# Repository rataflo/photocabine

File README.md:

# photocabine
Analogue photo booth

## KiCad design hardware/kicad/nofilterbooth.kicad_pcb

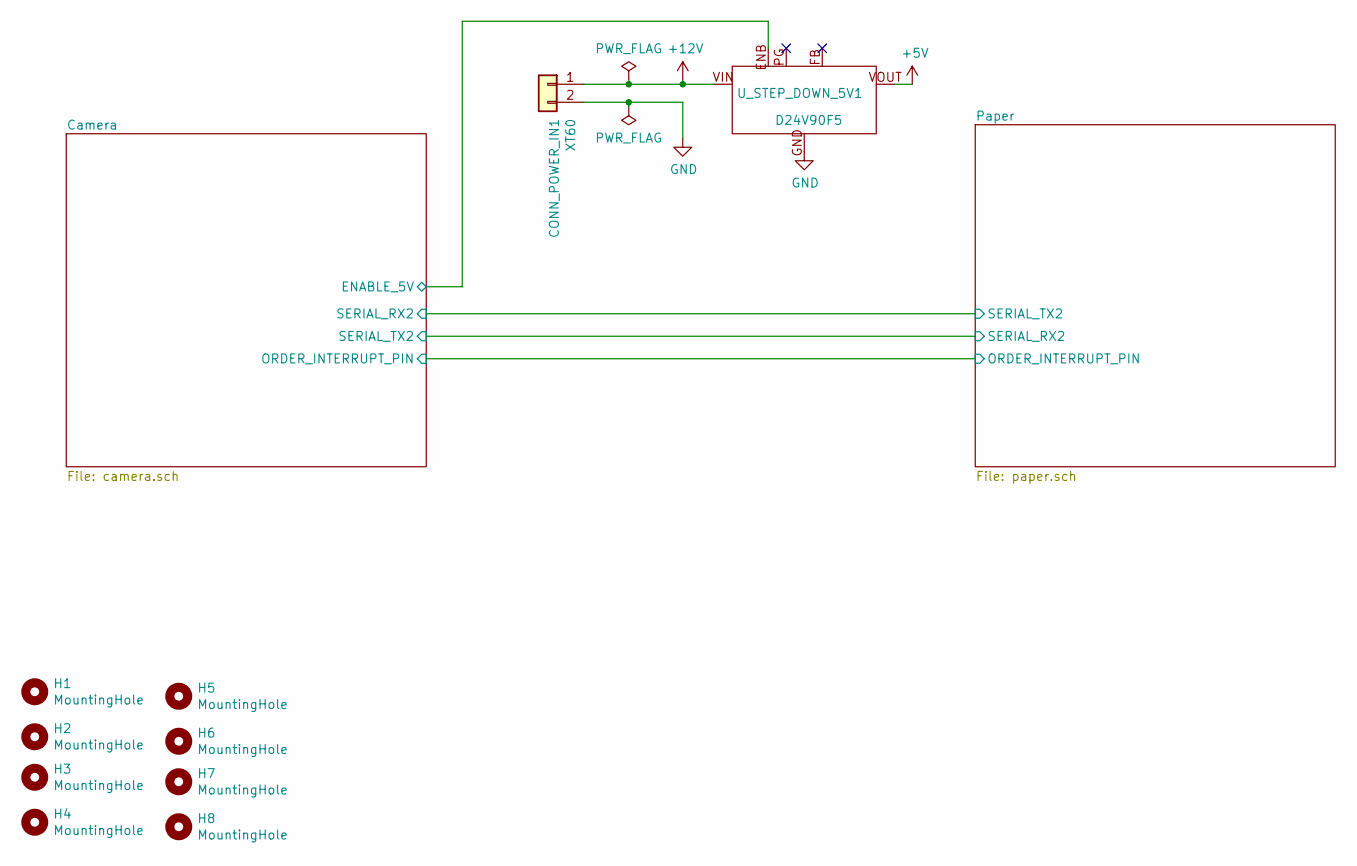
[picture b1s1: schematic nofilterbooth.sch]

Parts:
CONN_POWER_IN1: XT60; AMASS_XT60-F_1x02_P7.20mm_Vertical
H1, H2, H3, H4, H5, H6, H7, H8: MountingHole; MountingHole_3.2mm_M3
U_STEP_DOWN_5V1: D24V90F5

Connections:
+5V: U_STEP_DOWN_5V1.VOUT; also elsewhere on the board
+12V: CONN_POWER_IN1.1, U_STEP_DOWN_5V1.VIN; also elsewhere on the board
/Camera/ENABLE_5V: U_STEP_DOWN_5V1.ENB; also elsewhere on the board
GND: CONN_POWER_IN1.2, U_STEP_DOWN_5V1.GND; also elsewhere on the board

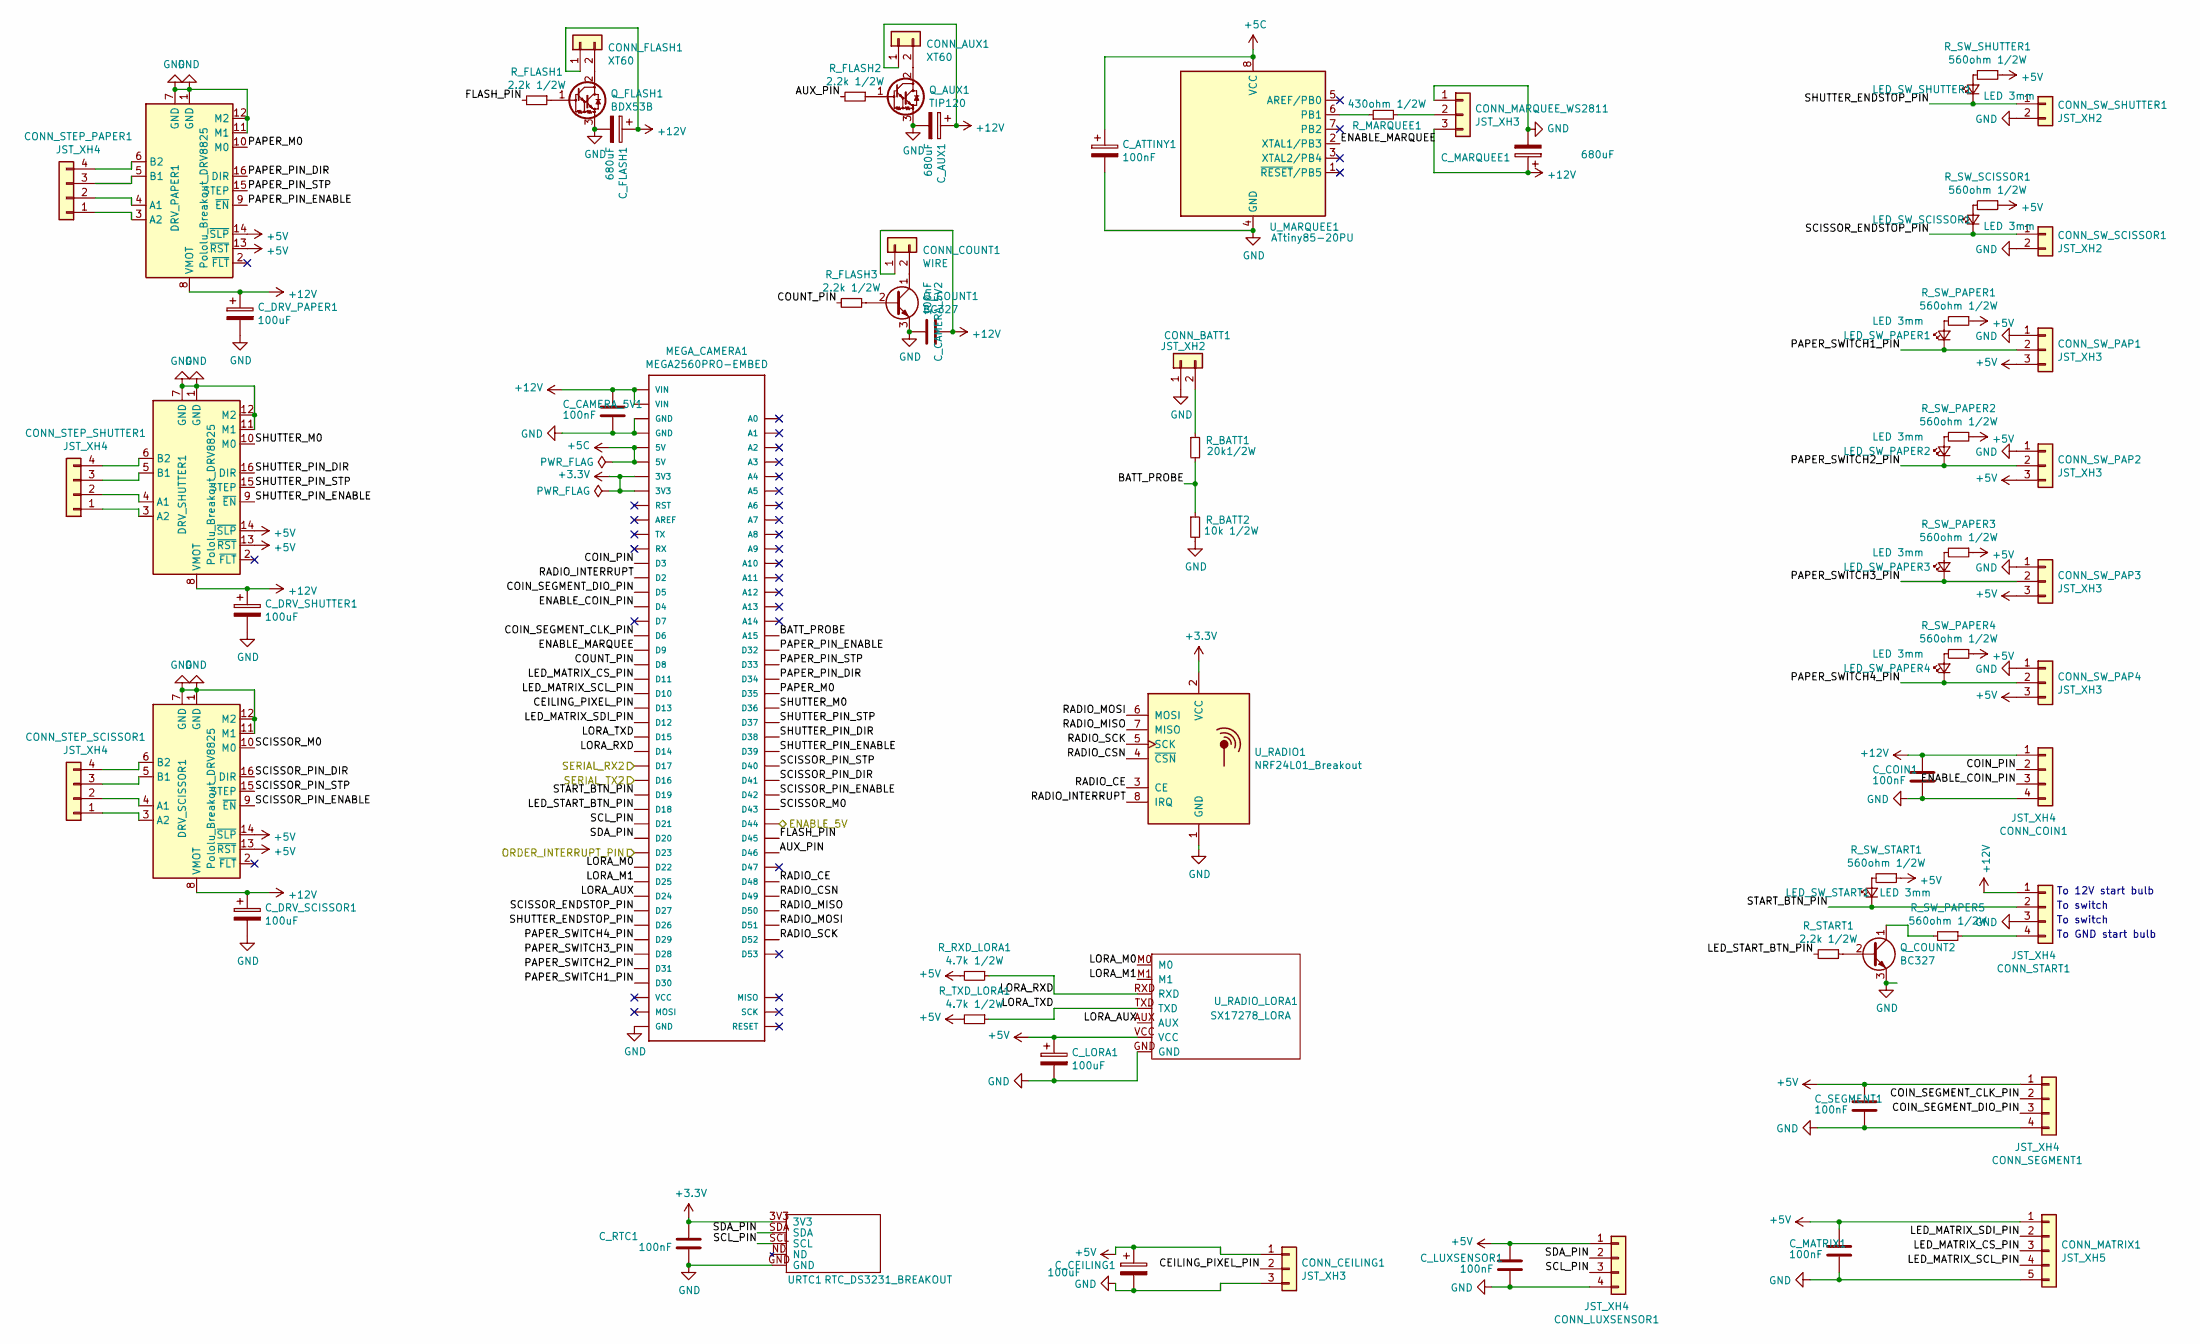
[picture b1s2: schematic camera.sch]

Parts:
CONN_AUX1: XT60; AMASS_XT60-F_1x02_P7.20mm_Vertical
CONN_BATT1: JST_XH2; JST_XH_S2B-XH-A-1_1x02_P2.50mm_Horizontal
CONN_CEILING1: JST_XH3; JST_XH_S3B-XH-A-1_1x03_P2.50mm_Horizontal
CONN_COIN1: JST_XH4; JST_XH_S4B-XH-A-1_1x04_P2.50mm_Horizontal
CONN_COUNT1: WIRE; PinHeader_1x02_P2.54mm_Vertical
CONN_FLASH1: XT60; AMASS_XT60-F_1x02_P7.20mm_Vertical
CONN_LUXSENSOR1: JST_XH4; JST_XH_S4B-XH-A-1_1x04_P2.50mm_Horizontal
CONN_MARQUEE_WS2811: JST_XH3; JST_XH_S3B-XH-A-1_1x03_P2.50mm_Horizontal
CONN_MATRIX1: JST_XH5; JST_XH_S5B-XH-A-1_1x05_P2.50mm_Horizontal
CONN_SEGMENT1: JST_XH4; JST_XH_S4B-XH-A-1_1x04_P2.50mm_Horizontal
CONN_START1: JST_XH4; JST_XH_S4B-XH-A-1_1x04_P2.50mm_Horizontal
CONN_STEP_PAPER1: JST_XH4; JST_XH_S4B-XH-A-1_1x04_P2.50mm_Horizontal
CONN_STEP_SCISSOR1: JST_XH4; JST_XH_S4B-XH-A-1_1x04_P2.50mm_Horizontal
CONN_STEP_SHUTTER1: JST_XH4; JST_XH_S4B-XH-A-1_1x04_P2.50mm_Horizontal
CONN_SW_PAP1, CONN_SW_PAP2, CONN_SW_PAP3, CONN_SW_PAP4: JST_XH3; JST_XH_S3B-XH-A-1_1x03_P2.50mm_Horizontal
CONN_SW_SCISSOR1: JST_XH2; JST_XH_S2B-XH-A-1_1x02_P2.50mm_Horizontal
CONN_SW_SHUTTER1: JST_XH2; JST_XH_S2B-XH-A-1_1x02_P2.50mm_Horizontal
C_ATTINY1: 100nF; C_Rect_L7.2mm_W2.5mm_P5.00mm_FKS2_FKP2_MKS2_MKP2
C_AUX1: 680uF; CP_Radial_D8.0mm_P3.50mm
C_CAMERA_5V1, C_CAMERA_5V2: 100nF; C_Rect_L7.2mm_W2.5mm_P5.00mm_FKS2_FKP2_MKS2_MKP2
C_CEILING1: 100uF; CP_Radial_D6.3mm_P2.50mm
C_COIN1: 100nF; C_Rect_L7.2mm_W2.5mm_P5.00mm_FKS2_FKP2_MKS2_MKP2
C_DRV_PAPER1: 100uF; CP_Radial_D6.3mm_P2.50mm
C_DRV_SCISSOR1: 100uF; CP_Radial_D6.3mm_P2.50mm
C_DRV_SHUTTER1: 100uF; CP_Radial_D6.3mm_P2.50mm
C_FLASH1: 680uF; CP_Radial_D8.0mm_P3.50mm
C_LORA1: 100uF; CP_Radial_D6.3mm_P2.50mm
C_LUXSENSOR1: 100nF; C_Rect_L7.2mm_W2.5mm_P5.00mm_FKS2_FKP2_MKS2_MKP2
C_MARQUEE1: 680uF; CP_Radial_D8.0mm_P3.50mm
C_MATRIX1: 100nF; C_Rect_L7.2mm_W2.5mm_P5.00mm_FKS2_FKP2_MKS2_MKP2
C_RTC1: 100nF; C_Rect_L7.2mm_W2.5mm_P5.00mm_FKS2_FKP2_MKS2_MKP2
C_SEGMENT1: 100nF; C_Rect_L7.2mm_W2.5mm_P5.00mm_FKS2_FKP2_MKS2_MKP2
DRV_PAPER1: Pololu_Breakout_DRV8825; Pololu_Breakout-16_15.2x20.3mm
DRV_SCISSOR1: Pololu_Breakout_DRV8825; Pololu_Breakout-16_15.2x20.3mm
DRV_SHUTTER1: Pololu_Breakout_DRV8825; Pololu_Breakout-16_15.2x20.3mm
LED_SW_PAPER1, LED_SW_PAPER2, LED_SW_PAPER3, LED_SW_PAPER4: LED 3mm; LED_D3.0mm
LED_SW_SCISSOR1: LED 3mm; LED_D3.0mm
LED_SW_SHUTTER1: LED 3mm; LED_D3.0mm
LED_SW_START1: LED 3mm; LED_D3.0mm
MEGA_CAMERA1: MEGA2560PRO-EMBED
Q_AUX1: TIP120; TO-220-3_Vertical
Q_COUNT1, Q_COUNT2: BC327; TO-92L_HandSolder
Q_FLASH1: BDX53B; TO-220-3_Vertical
R_BATT1: 20k1/2W; R_Axial_DIN0207_L6.3mm_D2.5mm_P10.16mm_Horizontal
R_BATT2: 10k 1/2W; R_Axial_DIN0207_L6.3mm_D2.5mm_P10.16mm_Horizontal
R_FLASH1, R_FLASH2, R_FLASH3: 2.2k 1/2W; R_Axial_DIN0207_L6.3mm_D2.5mm_P10.16mm_Horizontal
R_MARQUEE1: 430ohm 1/2W; R_Axial_DIN0207_L6.3mm_D2.5mm_P10.16mm_Horizontal
R_RXD_LORA1: 4.7k 1/2W; R_Axial_DIN0207_L6.3mm_D2.5mm_P10.16mm_Horizontal
R_START1: 2.2k 1/2W; R_Axial_DIN0207_L6.3mm_D2.5mm_P10.16mm_Horizontal
R_SW_PAPER1, R_SW_PAPER2, R_SW_PAPER3, R_SW_PAPER4, R_SW_PAPER5: 560ohm 1/2W; R_Axial_DIN0207_L6.3mm_D2.5mm_P10.16mm_Horizontal
R_SW_SCISSOR1: 560ohm 1/2W; R_Axial_DIN0207_L6.3mm_D2.5mm_P10.16mm_Horizontal
R_SW_SHUTTER1: 560ohm 1/2W; R_Axial_DIN0207_L6.3mm_D2.5mm_P10.16mm_Horizontal
R_SW_START1: 560ohm 1/2W; R_Axial_DIN0207_L6.3mm_D2.5mm_P10.16mm_Horizontal
R_TXD_LORA1: 4.7k 1/2W; R_Axial_DIN0207_L6.3mm_D2.5mm_P10.16mm_Horizontal
URTC1: RTC_DS3231_BREAKOUT; DS3231_breakout
U_MARQUEE1: ATtiny85-20PU; DIP-8_W7.62mm
U_RADIO1: NRF24L01_Breakout; nRF24L01_Breakout
U_RADIO_LORA1: SX17278_LORA; LORA_E32-TTL-100

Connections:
+3V3: C_RTC1.1, MEGA_CAMERA1.3V3, URTC1.3V3, U_RADIO1.2 (VCC)
+5C: C_ATTINY1.1, MEGA_CAMERA1.5V, U_MARQUEE1.8 (VCC)
+5V: CONN_CEILING1.1, CONN_LUXSENSOR1.1, CONN_MATRIX1.1, CONN_SEGMENT1.1, CONN_SW_PAP1.3, CONN_SW_PAP2.3, CONN_SW_PAP3.3, CONN_SW_PAP4.3, C_CEILING1.1, C_LORA1.1, C_LUXSENSOR1.1, C_MATRIX1.1, C_SEGMENT1.1, DRV_PAPER1.13 (~RST), DRV_PAPER1.14 (~SLP), DRV_SCISSOR1.13 (~RST), DRV_SCISSOR1.14 (~SLP), DRV_SHUTTER1.13 (~RST), DRV_SHUTTER1.14 (~SLP), R_RXD_LORA1.2, R_SW_PAPER1.1, R_SW_PAPER2.1, R_SW_PAPER3.1, R_SW_PAPER4.1, R_SW_SCISSOR1.1, R_SW_SHUTTER1.1, R_SW_START1.1, R_TXD_LORA1.2, U_RADIO_LORA1.VCC; also elsewhere on the board
+12V: CONN_AUX1.1, CONN_COIN1.1, CONN_COUNT1.1, CONN_FLASH1.1, CONN_MARQUEE_WS2811.3, CONN_START1.1, C_AUX1.1, C_CAMERA_5V1.1, C_CAMERA_5V2.1, C_COIN1.1, C_DRV_PAPER1.1, C_DRV_SCISSOR1.1, C_DRV_SHUTTER1.1, C_FLASH1.1, C_MARQUEE1.1, DRV_PAPER1.8 (VMOT), DRV_SCISSOR1.8 (VMOT), DRV_SHUTTER1.8 (VMOT), MEGA_CAMERA1.VIN; also elsewhere on the board
/AtoB: MEGA_CAMERA1.D17; also elsewhere on the board
/BtoA: MEGA_CAMERA1.D16; also elsewhere on the board
/Camera/A13: MEGA_CAMERA1.A13; also elsewhere on the board
/Camera/A14: MEGA_CAMERA1.A14; also elsewhere on the board
/Camera/AUX_PIN: MEGA_CAMERA1.D46, R_FLASH2.2
/Camera/BATT_PROBE: MEGA_CAMERA1.A15, R_BATT1.2, R_BATT2.1
/Camera/CEILING_PIXEL_PIN: CONN_CEILING1.2, MEGA_CAMERA1.D13
/Camera/COIN_PIN: CONN_COIN1.2, MEGA_CAMERA1.D3
/Camera/COIN_SEGMENT_CLK_PIN: CONN_SEGMENT1.2, MEGA_CAMERA1.D6
/Camera/COIN_SEGMENT_DIO_PIN: CONN_SEGMENT1.3, MEGA_CAMERA1.D5
/Camera/COUNT_PIN: MEGA_CAMERA1.D8, R_FLASH3.2
/Camera/D7: MEGA_CAMERA1.D7; also elsewhere on the board
/Camera/D47: MEGA_CAMERA1.D47; also elsewhere on the board
/Camera/D53: MEGA_CAMERA1.D53; also elsewhere on the board
/Camera/ENABLE_5V: MEGA_CAMERA1.D44; also elsewhere on the board
/Camera/ENABLE_COIN_PIN: CONN_COIN1.3, MEGA_CAMERA1.D4
/Camera/ENABLE_MARQUEE: MEGA_CAMERA1.D9, U_MARQUEE1.2 (XTAL1/PB3)
/Camera/FLASH_PIN: MEGA_CAMERA1.D45, R_FLASH1.2
/Camera/LED_MATRIX_CS_PIN: CONN_MATRIX1.3, MEGA_CAMERA1.D11
/Camera/LED_MATRIX_SCL_PIN: CONN_MATRIX1.4, MEGA_CAMERA1.D10
/Camera/LED_MATRIX_SDI_PIN: CONN_MATRIX1.2, MEGA_CAMERA1.D12
/Camera/LED_START_BTN_PIN: MEGA_CAMERA1.D18, R_START1.2
/Camera/LORA_AUX: MEGA_CAMERA1.D24, U_RADIO_LORA1.AUX
/Camera/LORA_M0: MEGA_CAMERA1.D22, U_RADIO_LORA1.M0
/Camera/LORA_M1: MEGA_CAMERA1.D25, U_RADIO_LORA1.M1
/Camera/LORA_RXD: MEGA_CAMERA1.D14, R_RXD_LORA1.1, U_RADIO_LORA1.RXD
/Camera/LORA_TXD: MEGA_CAMERA1.D15, R_TXD_LORA1.1, U_RADIO_LORA1.TXD
/Camera/ORDER_INTERRUPT_PIN: MEGA_CAMERA1.D23; also elsewhere on the board
/Camera/PAPER_M0: DRV_PAPER1.10 (M0), MEGA_CAMERA1.D35
/Camera/PAPER_PIN_DIR: DRV_PAPER1.16 (DIR), MEGA_CAMERA1.D34
/Camera/PAPER_PIN_ENABLE: DRV_PAPER1.9 (~EN), MEGA_CAMERA1.D32
/Camera/PAPER_PIN_STP: DRV_PAPER1.15 (STEP), MEGA_CAMERA1.D33
/Camera/PAPER_SWITCH1_PIN: CONN_SW_PAP1.2, LED_SW_PAPER1.1 (K), MEGA_CAMERA1.D30
/Camera/PAPER_SWITCH2_PIN: CONN_SW_PAP2.2, LED_SW_PAPER2.1 (K), MEGA_CAMERA1.D31
/Camera/PAPER_SWITCH3_PIN: CONN_SW_PAP3.2, LED_SW_PAPER3.1 (K), MEGA_CAMERA1.D28
/Camera/PAPER_SWITCH4_PIN: CONN_SW_PAP4.2, LED_SW_PAPER4.1 (K), MEGA_CAMERA1.D29
/Camera/RADIO_CE: MEGA_CAMERA1.D48, U_RADIO1.3 (CE)
/Camera/RADIO_CSN: MEGA_CAMERA1.D49, U_RADIO1.4 (~CSN)
/Camera/RADIO_INTERRUPT: MEGA_CAMERA1.D2, U_RADIO1.8 (IRQ)
/Camera/RADIO_MISO: MEGA_CAMERA1.D50, U_RADIO1.7 (MISO)
/Camera/RADIO_MOSI: MEGA_CAMERA1.D51, U_RADIO1.6 (MOSI)
/Camera/RADIO_SCK: MEGA_CAMERA1.D52, U_RADIO1.5 (SCK)
/Camera/SCISSOR_ENDSTOP_PIN: CONN_SW_SCISSOR1.1, LED_SW_SCISSOR1.1 (K), MEGA_CAMERA1.D27
/Camera/SCISSOR_M0: DRV_SCISSOR1.10 (M0), MEGA_CAMERA1.D43
/Camera/SCISSOR_PIN_DIR: DRV_SCISSOR1.16 (DIR), MEGA_CAMERA1.D41
/Camera/SCISSOR_PIN_ENABLE: DRV_SCISSOR1.9 (~EN), MEGA_CAMERA1.D42
/Camera/SCISSOR_PIN_STP: DRV_SCISSOR1.15 (STEP), MEGA_CAMERA1.D40
/Camera/SCL_PIN: CONN_LUXSENSOR1.3, MEGA_CAMERA1.D21, URTC1.SCL
/Camera/SDA_PIN: CONN_LUXSENSOR1.2, MEGA_CAMERA1.D20, URTC1.SDA
/Camera/SHUTTER_ENDSTOP_PIN: CONN_SW_SHUTTER1.1, LED_SW_SHUTTER1.1 (K), MEGA_CAMERA1.D26
/Camera/SHUTTER_M0: DRV_SHUTTER1.10 (M0), MEGA_CAMERA1.D36
/Camera/SHUTTER_PIN_DIR: DRV_SHUTTER1.16 (DIR), MEGA_CAMERA1.D38
/Camera/SHUTTER_PIN_ENABLE: DRV_SHUTTER1.9 (~EN), MEGA_CAMERA1.D39
/Camera/SHUTTER_PIN_STP: DRV_SHUTTER1.15 (STEP), MEGA_CAMERA1.D37
/Camera/START_BTN_PIN: CONN_START1.2, LED_SW_START1.1 (K), MEGA_CAMERA1.D19
GND: CONN_BATT1.1, CONN_CEILING1.3, CONN_COIN1.4, CONN_LUXSENSOR1.4, CONN_MARQUEE_WS2811.1, CONN_MATRIX1.5, CONN_SEGMENT1.4, CONN_START1.3, CONN_SW_PAP1.1, CONN_SW_PAP2.1, CONN_SW_PAP3.1, CONN_SW_PAP4.1, CONN_SW_SCISSOR1.2, CONN_SW_SHUTTER1.2, C_ATTINY1.2, C_AUX1.2, C_CAMERA_5V1.2, C_CAMERA_5V2.2, C_CEILING1.2, C_COIN1.2, C_DRV_PAPER1.2, C_DRV_SCISSOR1.2, C_DRV_SHUTTER1.2, C_FLASH1.2, C_LORA1.2, C_LUXSENSOR1.2, C_MARQUEE1.2, C_MATRIX1.2, C_RTC1.2, C_SEGMENT1.2, DRV_PAPER1.1 (GND), DRV_PAPER1.7 (GND), DRV_PAPER1.11 (M1), DRV_PAPER1.12 (M2), DRV_SCISSOR1.1 (GND), DRV_SCISSOR1.7 (GND), DRV_SCISSOR1.11 (M1), DRV_SCISSOR1.12 (M2), DRV_SHUTTER1.1 (GND), DRV_SHUTTER1.7 (GND), DRV_SHUTTER1.11 (M1), DRV_SHUTTER1.12 (M2), MEGA_CAMERA1.GND, Q_AUX1.3 (E), Q_COUNT1.3 (E), Q_COUNT2.3 (E), Q_FLASH1.3 (E), R_BATT2.2, URTC1.GND, U_MARQUEE1.4 (GND), U_RADIO1.1 (GND), U_RADIO_LORA1.GND; also elsewhere on the board
unnamed: CONN_AUX1.2, Q_AUX1.2 (C)
unnamed: CONN_BATT1.2, R_BATT1.1
unnamed: CONN_COUNT1.2, Q_COUNT1.1 (C)
unnamed: CONN_FLASH1.2, Q_FLASH1.2 (C)
unnamed: CONN_MARQUEE_WS2811.2, R_MARQUEE1.2
unnamed 81: CONN_START1.4, R_SW_PAPER5.1; also elsewhere on the board
unnamed: CONN_STEP_PAPER1.1, DRV_PAPER1.3 (A2)
unnamed: CONN_STEP_PAPER1.2, DRV_PAPER1.4 (A1)
unnamed: CONN_STEP_PAPER1.3, DRV_PAPER1.5 (B1)
unnamed: CONN_STEP_PAPER1.4, DRV_PAPER1.6 (B2)
unnamed: CONN_STEP_SCISSOR1.1, DRV_SCISSOR1.3 (A2)
unnamed: CONN_STEP_SCISSOR1.2, DRV_SCISSOR1.4 (A1)
unnamed: CONN_STEP_SCISSOR1.3, DRV_SCISSOR1.5 (B1)
unnamed: CONN_STEP_SCISSOR1.4, DRV_SCISSOR1.6 (B2)
unnamed: CONN_STEP_SHUTTER1.1, DRV_SHUTTER1.3 (A2)
unnamed: CONN_STEP_SHUTTER1.2, DRV_SHUTTER1.4 (A1)
unnamed: CONN_STEP_SHUTTER1.3, DRV_SHUTTER1.5 (B1)
unnamed: CONN_STEP_SHUTTER1.4, DRV_SHUTTER1.6 (B2)
unnamed: LED_SW_PAPER1.2 (A), R_SW_PAPER1.2
unnamed: LED_SW_PAPER2.2 (A), R_SW_PAPER2.2
unnamed: LED_SW_PAPER3.2 (A), R_SW_PAPER3.2
unnamed: LED_SW_PAPER4.2 (A), R_SW_PAPER4.2
unnamed: LED_SW_SCISSOR1.2 (A), R_SW_SCISSOR1.2
unnamed: LED_SW_SHUTTER1.2 (A), R_SW_SHUTTER1.2
unnamed: LED_SW_START1.2 (A), R_SW_START1.2
unnamed: Q_AUX1.1 (B), R_FLASH2.1
unnamed: Q_COUNT1.2 (B), R_FLASH3.1
unnamed: Q_COUNT2.1 (C), R_SW_PAPER5.2
unnamed: Q_FLASH1.1 (B), R_FLASH1.1
unnamed 120: Q_COUNT2.2 (B), R_START1.1; also elsewhere on the board
unnamed: R_MARQUEE1.1, U_MARQUEE1.6 (PB1)

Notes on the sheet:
To GND start bulb
To 12V start bulb
To switch

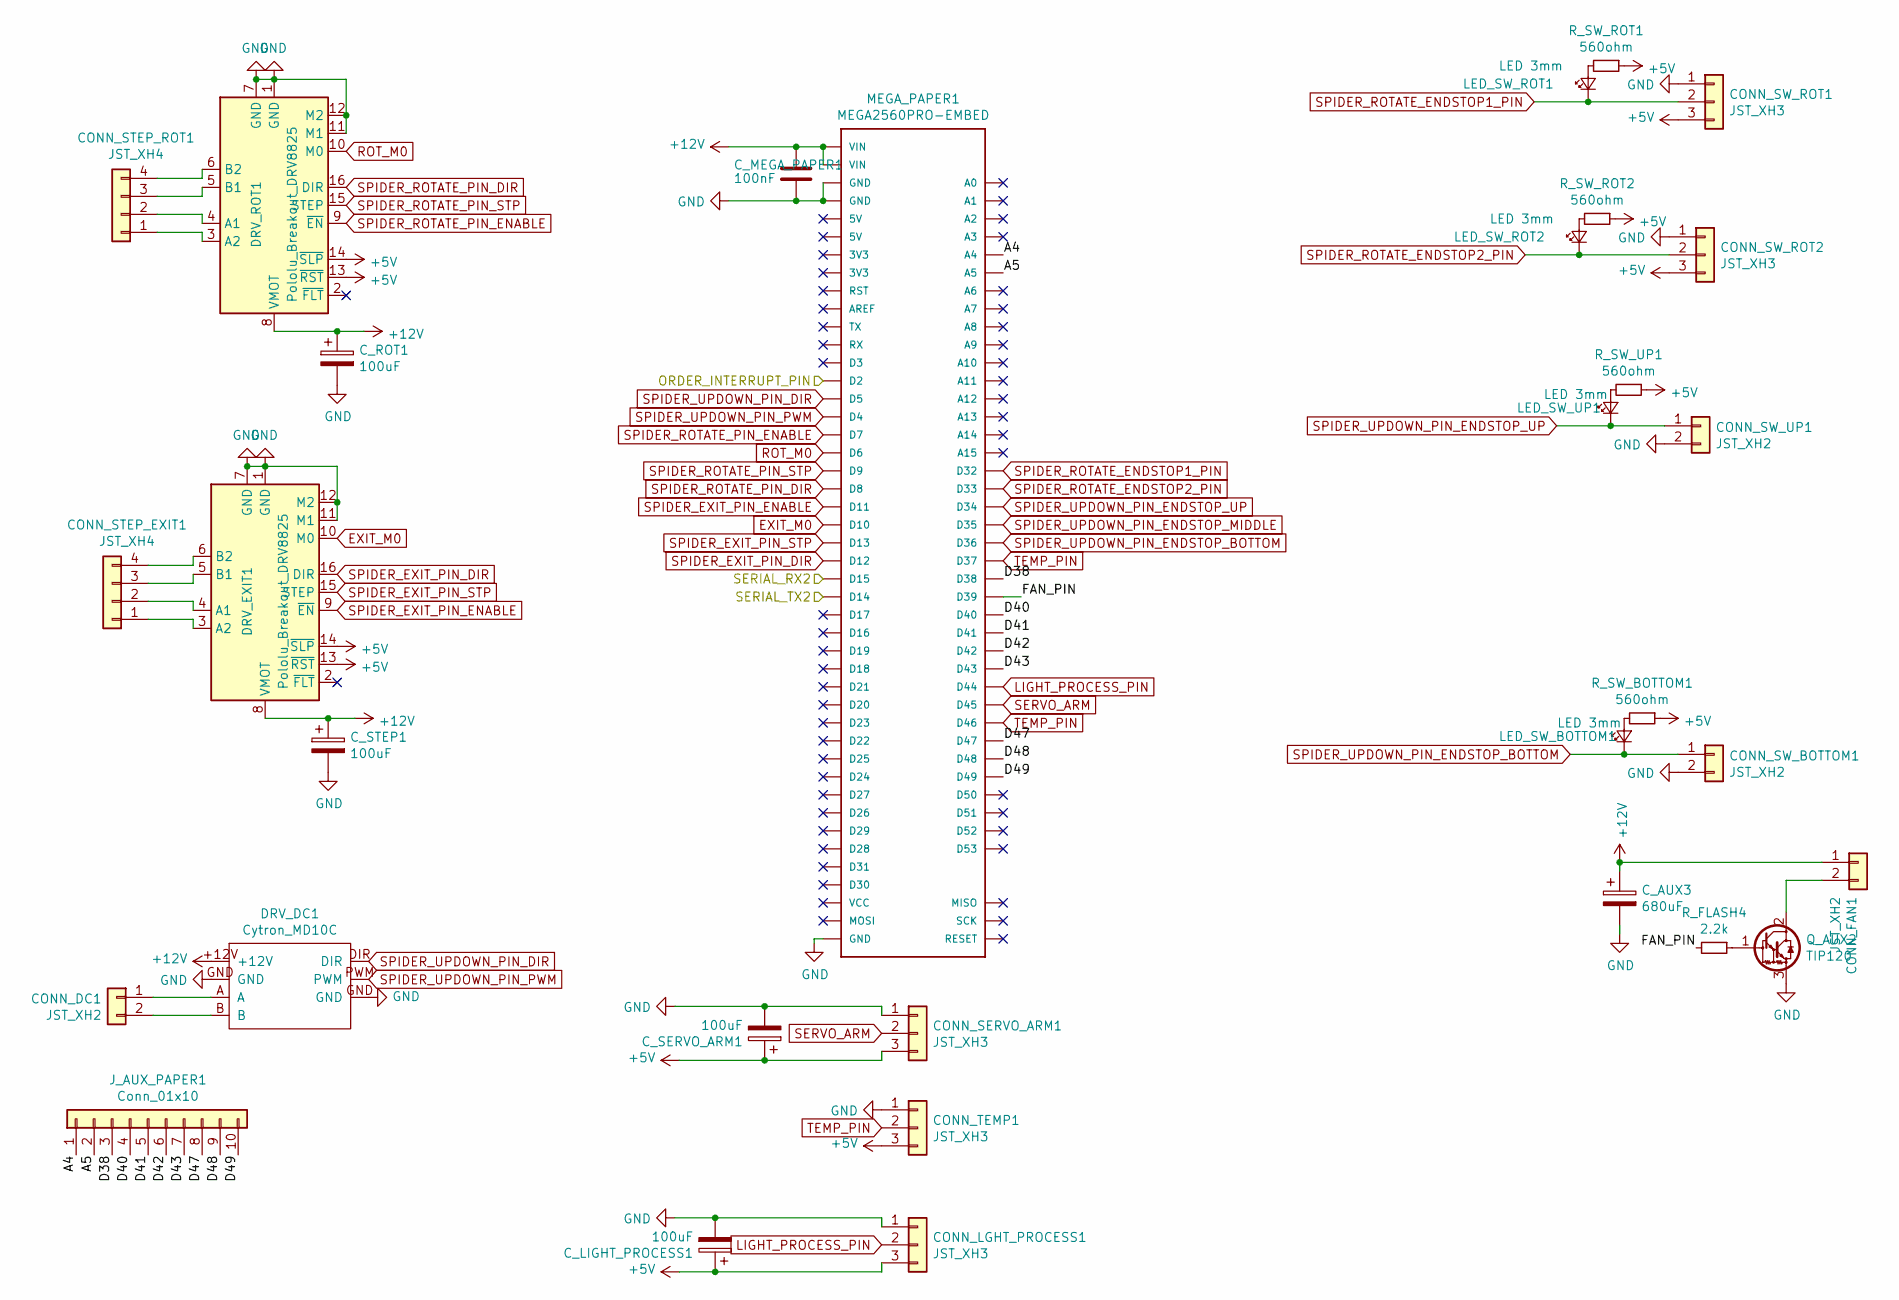
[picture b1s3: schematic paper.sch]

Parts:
CONN_DC1: JST_XH2; JST_XH_S2B-XH-A-1_1x02_P2.50mm_Horizontal
CONN_FAN1: JST_XH2; JST_XH_S2B-XH-A-1_1x02_P2.50mm_Horizontal
CONN_LGHT_PROCESS1: JST_XH3; JST_XH_S3B-XH-A-1_1x03_P2.50mm_Horizontal
CONN_SERVO_ARM1: JST_XH3; JST_XH_S3B-XH-A-1_1x03_P2.50mm_Horizontal
CONN_STEP_EXIT1: JST_XH4; JST_XH_S4B-XH-A-1_1x04_P2.50mm_Horizontal
CONN_STEP_ROT1: JST_XH4; JST_XH_S4B-XH-A-1_1x04_P2.50mm_Horizontal
CONN_SW_BOTTOM1: JST_XH2; JST_XH_S2B-XH-A-1_1x02_P2.50mm_Horizontal
CONN_SW_ROT1, CONN_SW_ROT2: JST_XH3; JST_XH_S3B-XH-A-1_1x03_P2.50mm_Horizontal
CONN_SW_UP1: JST_XH2; JST_XH_S2B-XH-A-1_1x02_P2.50mm_Horizontal
CONN_TEMP1: JST_XH3; JST_XH_S3B-XH-A-1_1x03_P2.50mm_Horizontal
C_AUX3: 680uF; CP_Radial_D8.0mm_P3.50mm
C_LIGHT_PROCESS1: 100uF; CP_Radial_D6.3mm_P2.50mm
C_MEGA_PAPER1: 100nF; C_Rect_L7.2mm_W2.5mm_P5.00mm_FKS2_FKP2_MKS2_MKP2
C_ROT1: 100uF; CP_Radial_D6.3mm_P2.50mm
C_SERVO_ARM1: 100uF; CP_Radial_D6.3mm_P2.50mm
C_STEP1: 100uF; CP_Radial_D6.3mm_P2.50mm
DRV_DC1: Cytron_MD10C; CYTRON_MD10C
DRV_EXIT1: Pololu_Breakout_DRV8825; Pololu_Breakout-16_15.2x20.3mm
DRV_ROT1: Pololu_Breakout_DRV8825; Pololu_Breakout-16_15.2x20.3mm
J_AUX_PAPER1: Conn_01x10; PinHeader_1x10_P2.54mm_Vertical
LED_SW_BOTTOM1: LED 3mm; LED_D3.0mm
LED_SW_ROT1, LED_SW_ROT2: LED 3mm; LED_D3.0mm
LED_SW_UP1: LED 3mm; LED_D3.0mm
MEGA_PAPER1: MEGA2560PRO-EMBED
Q_AUX2: TIP120; TO-220-3_Vertical
R_FLASH4: 2.2k; R_Axial_DIN0207_L6.3mm_D2.5mm_P10.16mm_Horizontal
R_SW_BOTTOM1: 560ohm; R_Axial_DIN0207_L6.3mm_D2.5mm_P10.16mm_Horizontal
R_SW_ROT1, R_SW_ROT2: 560ohm; R_Axial_DIN0207_L6.3mm_D2.5mm_P10.16mm_Horizontal
R_SW_UP1: 560ohm; R_Axial_DIN0207_L6.3mm_D2.5mm_P10.16mm_Horizontal

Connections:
+5V: CONN_LGHT_PROCESS1.3, CONN_SERVO_ARM1.3, CONN_SW_ROT1.3, CONN_SW_ROT2.3, CONN_TEMP1.3, C_LIGHT_PROCESS1.1, C_SERVO_ARM1.1, DRV_EXIT1.13 (~RST), DRV_EXIT1.14 (~SLP), DRV_ROT1.13 (~RST), DRV_ROT1.14 (~SLP), R_SW_BOTTOM1.1, R_SW_ROT1.1, R_SW_ROT2.1, R_SW_UP1.1; also elsewhere on the board
+12V: CONN_FAN1.1, C_AUX3.1, C_MEGA_PAPER1.1, C_ROT1.1, C_STEP1.1, DRV_DC1.+12V, DRV_EXIT1.8 (VMOT), DRV_ROT1.8 (VMOT), MEGA_PAPER1.VIN; also elsewhere on the board
/AtoB: MEGA_PAPER1.D14; also elsewhere on the board
/BtoA: MEGA_PAPER1.D15; also elsewhere on the board
/Camera/ORDER_INTERRUPT_PIN: MEGA_PAPER1.D2; also elsewhere on the board
/Paper/A4: J_AUX_PAPER1.1, MEGA_PAPER1.A4
/Paper/A5: J_AUX_PAPER1.2, MEGA_PAPER1.A5
/Paper/D38: J_AUX_PAPER1.3, MEGA_PAPER1.D38
/Paper/D40: J_AUX_PAPER1.4, MEGA_PAPER1.D40
/Paper/D41: J_AUX_PAPER1.5, MEGA_PAPER1.D41
/Paper/D42: J_AUX_PAPER1.6, MEGA_PAPER1.D42
/Paper/D43: J_AUX_PAPER1.7, MEGA_PAPER1.D43
/Paper/D47: J_AUX_PAPER1.8, MEGA_PAPER1.D47
/Paper/D48: J_AUX_PAPER1.9, MEGA_PAPER1.D48
/Paper/D49: J_AUX_PAPER1.10, MEGA_PAPER1.D49
/Paper/FAN_PIN: MEGA_PAPER1.D39, R_FLASH4.2
EXIT_M0: DRV_EXIT1.10 (M0), MEGA_PAPER1.D10
GND: CONN_LGHT_PROCESS1.1, CONN_SERVO_ARM1.1, CONN_SW_BOTTOM1.2, CONN_SW_ROT1.1, CONN_SW_ROT2.1, CONN_SW_UP1.2, CONN_TEMP1.1, C_AUX3.2, C_LIGHT_PROCESS1.2, C_MEGA_PAPER1.2, C_ROT1.2, C_SERVO_ARM1.2, C_STEP1.2, DRV_DC1.GND, DRV_EXIT1.1 (GND), DRV_EXIT1.7 (GND), DRV_EXIT1.11 (M1), DRV_EXIT1.12 (M2), DRV_ROT1.1 (GND), DRV_ROT1.7 (GND), DRV_ROT1.11 (M1), DRV_ROT1.12 (M2), MEGA_PAPER1.GND, Q_AUX2.3 (E); also elsewhere on the board
LIGHT_PROCESS_PIN: CONN_LGHT_PROCESS1.2, MEGA_PAPER1.D44
unnamed: CONN_DC1.1, DRV_DC1.A
unnamed: CONN_DC1.2, DRV_DC1.B
unnamed: CONN_FAN1.2, Q_AUX2.2 (C)
unnamed: CONN_STEP_EXIT1.1, DRV_EXIT1.3 (A2)
unnamed: CONN_STEP_EXIT1.2, DRV_EXIT1.4 (A1)
unnamed: CONN_STEP_EXIT1.3, DRV_EXIT1.5 (B1)
unnamed: CONN_STEP_EXIT1.4, DRV_EXIT1.6 (B2)
unnamed: CONN_STEP_ROT1.1, DRV_ROT1.3 (A2)
unnamed: CONN_STEP_ROT1.2, DRV_ROT1.4 (A1)
unnamed: CONN_STEP_ROT1.3, DRV_ROT1.5 (B1)
unnamed: CONN_STEP_ROT1.4, DRV_ROT1.6 (B2)
unnamed: LED_SW_BOTTOM1.2 (A), R_SW_BOTTOM1.2
unnamed: LED_SW_ROT1.2 (A), R_SW_ROT1.2
unnamed: LED_SW_ROT2.2 (A), R_SW_ROT2.2
unnamed: LED_SW_UP1.2 (A), R_SW_UP1.2
unnamed: Q_AUX2.1 (B), R_FLASH4.1
ROT_M0: DRV_ROT1.10 (M0), MEGA_PAPER1.D6
SERVO_ARM: CONN_SERVO_ARM1.2, MEGA_PAPER1.D45
SPIDER_EXIT_PIN_DIR: DRV_EXIT1.16 (DIR), MEGA_PAPER1.D12
SPIDER_EXIT_PIN_ENABLE: DRV_EXIT1.9 (~EN), MEGA_PAPER1.D11
SPIDER_EXIT_PIN_STP: DRV_EXIT1.15 (STEP), MEGA_PAPER1.D13
SPIDER_ROTATE_ENDSTOP1_PIN: CONN_SW_ROT1.2, LED_SW_ROT1.1 (K), MEGA_PAPER1.D32
SPIDER_ROTATE_ENDSTOP2_PIN: CONN_SW_ROT2.2, LED_SW_ROT2.1 (K), MEGA_PAPER1.D33
SPIDER_ROTATE_PIN_DIR: DRV_ROT1.16 (DIR), MEGA_PAPER1.D8
SPIDER_ROTATE_PIN_ENABLE: DRV_ROT1.9 (~EN), MEGA_PAPER1.D7
SPIDER_ROTATE_PIN_STP: DRV_ROT1.15 (STEP), MEGA_PAPER1.D9
SPIDER_UPDOWN_PIN_DIR: DRV_DC1.DIR, MEGA_PAPER1.D5
SPIDER_UPDOWN_PIN_ENDSTOP_BOTTOM: CONN_SW_BOTTOM1.1, LED_SW_BOTTOM1.1 (K), MEGA_PAPER1.D36
SPIDER_UPDOWN_PIN_ENDSTOP_UP: CONN_SW_UP1.1, LED_SW_UP1.1 (K), MEGA_PAPER1.D34
SPIDER_UPDOWN_PIN_PWM: DRV_DC1.PWM, MEGA_PAPER1.D4
TEMP_PIN: CONN_TEMP1.2, MEGA_PAPER1.D37, MEGA_PAPER1.D46

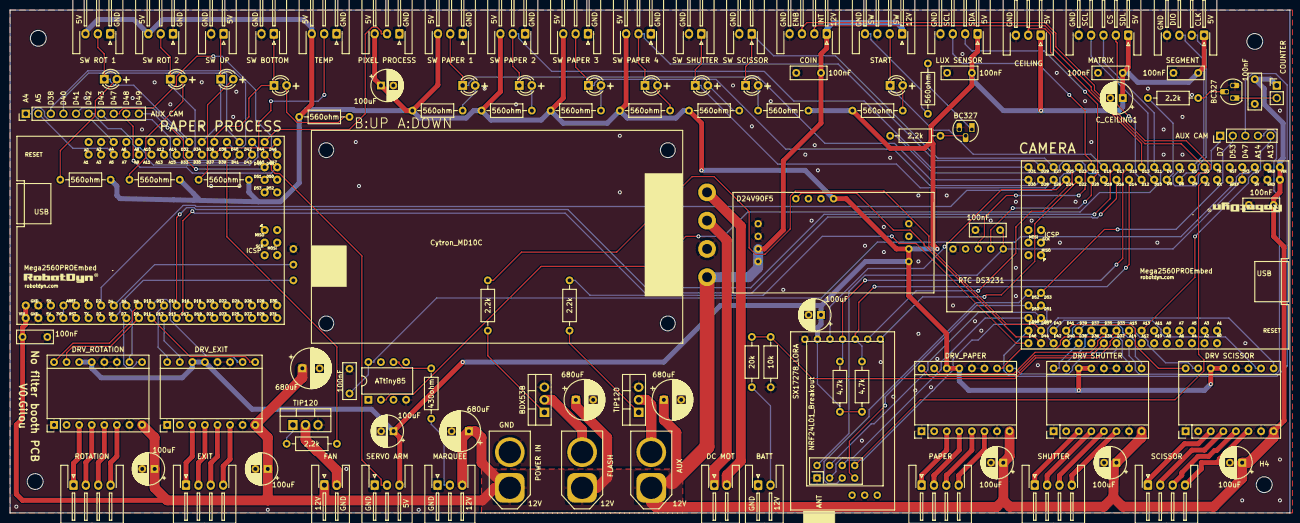
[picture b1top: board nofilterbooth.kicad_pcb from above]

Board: 2 copper layers, 258.6 x 101.6 mm, 111 parts (0 on the bottom side), 135 nets.

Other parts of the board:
J_AUX_CAM1: Conn_01x10; PinHeader_1x05_P2.54mm_Vertical
Q_START1: BC327; TO-92L_HandSolder
R_LED_START1: 560ohm; R_Axial_DIN0207_L6.3mm_D2.5mm_P10.16mm_Horizontal

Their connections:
/Camera/A13: J_AUX_CAM1.5; also elsewhere on the board
/Camera/A14: J_AUX_CAM1.4; also elsewhere on the board
/Camera/D7: J_AUX_CAM1.1; also elsewhere on the board
/Camera/D47: J_AUX_CAM1.3; also elsewhere on the board
/Camera/D53: J_AUX_CAM1.2; also elsewhere on the board
GND: Q_START1.3; also elsewhere on the board
unnamed 81: R_LED_START1.1; also elsewhere on the board
unnamed: Q_START1.1, R_LED_START1.2
unnamed 120: Q_START1.2; also elsewhere on the board

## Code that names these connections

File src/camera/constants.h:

#ifndef constants_h
#define constants_h

#include "Arduino.h"

// uncomment to activate debug and serial output.
#define DEBUG_MODE

#define SHUTTER_PIN_STP 23
#define SHUTTER_PIN_DIR 22
#define SHUTTER_ENDSTOP_PIN 53
#define SHUTTER_PIN_ENABLE 31

#define LED_MATRIX_SDI_PIN 12 // SDI = DIN
#define LED_MATRIX_CS_PIN 11 // CS
#define LED_MATRIX_SCL_PIN 10 // SCL = CLOCK

#define SCISSOR_PIN_STP 25
#define SCISSOR_PIN_DIR 24
#define SCISSOR_ENDSTOP_PIN 40
#define SCISSOR_SPEED 200
#define SCISSOR_ACCEL 200
#define SCISSOR_STEP_OPENED 350 // Number of step to fully open the scissor.
#define SCISSOR_PIN_ENABLE 33

#define PAPER_PIN_STP 27
#define PAPER_PIN_DIR 26
#define NB_STEP_PAPER_ONE_SHOT 730 // Number of step to move to another shot.
#define NB_STEP_PAPER_OUT 3330 // Number of step to move out paper. //3230
#define PAPER_SPEED 500
#define PAPER_ACCEL 500
#define DELTA_FIRST_SHOT -80 //Delta in step to do after paper reach opto 1.
#define PAPER_SWITCH1_PIN 48
#define PAPER_SWITCH2_PIN 49
#define PAPER_SWITCH3_PIN 36 // TODO: Changer de 50 à 54
#define PAPER_SWITCH4_PIN 37 // TODO: Changer de 51 à 55
#define PAPER_PIN_ENABLE 35

#define FLASH_PIN 46
#define AUX_PIN 42
#define START_BTN_PIN 45
#define LED_START_BTN_PIN 47

#define COIN_PIN 3 // Add 10k/100k pull up resistor on pin to 5V.
#define ENABLE_COIN_PIN 44 // If High coin acceptor is enable. LOW coin acceptor reject coins.
#define COIN_SEGMENT_CLK_PIN 6
#define COIN_SEGMENT_DIO_PIN 5 // TODO : Changer de 7 à 5

const byte RADIO_ADRESS_EMITTER[6] = "00002";
const byte RADIO_ADRESS_RECEIVER[6] = "00001";

#define RADIO_CSN 8
#define RADIO_CE 7
#define RADIO_SCK 52 // Fixed SPI pin on arduino mega
#define RADIO_MOSI 51 // Fixed SPI pin on arduino mega
#define RADIO_MISO 50 // Fixed SPI pin on arduino mega
#define RADIO_INTERRUPT 2

#define ORDER_INTERRUPT_PIN 43

#define WAIT_BETWEEN_SHOT 5000 // Wait between shot in ms.

// Modes and prices
#define PRICE_CTS 200 // Price of a photo in cents.
#define FREE_PRICE_CTS 100 // Minimum in free price mode
#define MODE_PAYING 0
#define MODE_FREE_PRICE 1
#define MODE_FREE 2

// ceiling lamp
#define CEILING_PIXEL_PIN 13
#define CEILING_NBPIXEL 40

// EEPROM data & work variables
#define EEPROM_ADRESS 0
struct storage {
  byte checkCode = 0;
  int totStrip = 0;
  byte mode = 0;// O = paying, 1 = Free price, 2 = Free
  float totMoney = 0;
  int price_cts = 200;
  int free_price_cts = 100;
  int tank_time = 18000;
};

#endif

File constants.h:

// X: 22 / 23 
// Y: 24 / 25
// Z: 30 / 31
// Ext: 26 / 27

#define SHUTTER_PIN_STP 30
#define SHUTTER_PIN_DIR 31
#define SHUTTER_ENDSTOP_PIN 53
#define SHUTTER_STEPPER_SPEED 8

#define SCISSOR_PIN_STP 22
#define SCISSOR_PIN_DIR 23
#define SCISSOR_ENDSTOP_PIN 52
#define SCISSOR_STEPPER_SPEED 2
#define SCISSOR_STEP_OPENED -100 // Number of step to fully open the scissor.

#define PAPER_PIN_STP 24
#define PAPER_PIN_DIR 25
#define PAPER_STEPPER_SPEED 3
#define NB_STEP_ONE_SHOT 100 // Number of step to move to another shot.

#define SPIDER_UPDOWN_PIN_UP 45
#define SPIDER_UPDOWN_PIN_DOWN 44
#define SPIDER_UPDOWN_ENDSTOP_PIN 48
#define SPIDER_UPDOWN_STEPPER_SPEED 10

#define SPIDER_ROTATE_PIN_STP 32
#define SPIDER_ROTATE_PIN_DIR 33
#define SPIDER_UPDOWN_BOTTOM_ENDSTOP_PIN 36
#define SPIDER_UPDOWN_UPPER_ENDSTOP_PIN 37
#define SPIDER_ROTATE_NBSTEP 406 // Number of steps to mode to one tank
#define SPIDER_ROTATE_ENDSTOP_PIN 38

#define SERVO_ARM 46
#define SERVO_ARM_IDLE_POS 70
#define SERVO_ARM_OPEN_POS 00
#define SERVO_ARM_CLOSE_POS 180

#define FLASH_PIN 47

#define START_BTN_PIN 42
#define LED_START_BTN_PIN 43

#define MENU_BTN1_PIN 50
#define MENU_BTN2_PIN 51
#define MENU_SPEED 200 // check button menu each 200ms (digitalSerialRead is time consuming).

#define COIN_PIN 3 // Add 10k/100k pull up resistor on pin to 5V.
#define ENABLE_COIN_PIN 5 // If High coin acceptor is enable. LOW coin acceptor reject coins.
#define PRICE_CTS 200 // Price of a photo in cents.

#define WAIT_BETWEEN_SHOT 5000 // Wait between shot in ms.

// Define menu structure.
typedef struct
{
    byte id; 
    String label; 
    byte parentMenu;
}menuItem;

#define TAILLE_MENU 25
const menuItem MENUS[TAILLE_MENU] = {
  {1, "...                ", 0},
  {2, "Pause              ", 0},
  {3, "Take shot          ", 0},
  {4, "Setup              ", 0},
  {5, "Tests              ", 0},
  {6, "...                ", 5},
  {7, "Steppers           ", 5},
  {8, "Microswitchs       ", 5},
  {9, "LED                ", 5},
  {10,"Relay              ", 5},
  {11,"...                ", 7},
  {12,"Shutter            ", 7},
  {13,"Scissor            ", 7},
  {14,"Paper feeder       ", 7},
  {15,"Spider up/down     ", 7},
  {16,"Spider rotate      ", 7},
  {17,"Paper exit         ", 7},
  {18,"...                ", 8},
  {19,"Switch shutter     ", 8},
  {20,"Switch scissor     ", 8},
  {21,"Switch up&down     ", 8},
  {22,"Start              ", 8},
  {23,"...                ", 9},
  {24,"Flash on           ", 9},
  {25,"Start LED on       ", 9},
};

String sel = ">";
String espace = " ";

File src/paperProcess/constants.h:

#ifndef constants_h
#define constants_h

// uncomment to activate debug and serial output.
#define DEBUG_MODE

#define SPIDER_UPDOWN_PIN_DIR 11
#define SPIDER_UPDOWN_PIN_PWM 3 // Use pin 3 because on other pin the pwm is disabled by DirectIO.
#define SPIDER_UPDOWN_PIN_ENDSTOP_UP 12
#define SPIDER_UPDOWN_PIN_ENDSTOP_BOTTOM 4
#define SPIDER_UPDOWN_PIN_ENDSTOP_MIDDLE 45
#define SPIDER_UPDOWN_MAX_SPEED 255
#define SPIDER_UPDOWN_LOW_SPEED 95 //TODO: check other speed for sound level.

#define SPIDER_ROTATE_PIN_STP 23
#define SPIDER_ROTATE_PIN_DIR 22
#define SPIDER_ROTATE_NBSTEP 450 // Number of steps to move to one tank
#define SPIDER_ROTATE_ENDSTOP1_PIN 47 // Endstop in front of paper exit. Pair
#define SPIDER_ROTATE_ENDSTOP2_PIN 46 // Endstop 1/14 degrees right from endstop 1. Impair
#define SPIDER_ROTATE_SPEED 500
#define SPIDER_ROTATE_ACCEL 100
#define SPIDER_ROTATE_PIN_ENABLE 25 // TODO: check if rigth pin.


#define SERVO_ARM 6
#define SERVO_ARM_IDLE_POS 35
#define SERVO_ARM_OPEN_POS_BEGIN 0 
#define SERVO_ARM_OPEN_POS_END 140
#define SERVO_ARM_CLOSE_POS_BEGIN 190
#define SERVO_ARM_CLOSE_POS_END 20

#define SPIDER_EXIT_PIN_STP 10
#define SPIDER_EXIT_PIN_DIR 13
#define SPIDER_EXIT_PIN_ENABLE 7
#define SPIDER_EXIT_SPEED 500
#define SPIDER_EXIT_ACCEL 50
//#define SPIDER_EXIT_PIN_SWITCH not connected for now

#define LEDSTRIP_PIN 9 // TODO : Change pin.
#define LEDSTRIP_NB 84
#define TANK_TIME 18000 // Default time in each tank. Temperature between 32°C and 40°C.
#define DELIVERY_TIME 5000 // Time to exit paper

#define TEMP_PIN 8
#define ORDER_INTERRUPT_PIN 2

// SLOT STATE
#define SLOT_NO_ARM 0 // 0 = no arm, 
#define SLOT_CLOSED 1 // 1 = arm closed
#define SLOT_OPEN 2 // 2 = arm open, 
#define SLOT_PAPER 3 // 3 = arm open with paper.

// EEPROM data
#define EEPROM_ADRESS 0 // Lot of update/read so change adress from time to time to avoid corrupted memory.
struct storage {
  byte checkCode = 222;
  int tankTime = TANK_TIME;
  byte slots[14];
};

#endif

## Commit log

2018-02-22 feat: Init project
2018-02-22 feat : 3d model
2018-02-27 feat: servo arm init
2018-03-10 dc motor, button start
2018-03-11 test library fast read & write
2018-03-11 Use of DirectIO for fast read & write
2018-03-18 refactor: move spider code to second arduino.
2018-03-27 Add segment display and led matrix
2018-04-13 feat: more feats
2018-04-23 feat: i2c + debug
2018-05-10 fix fix fix
2018-05-14 fix after thsf & remove DiretIO library.
2018-09-06 Modif code tests THSF.
2019-01-24 Begin of complete refactor. Use Serial instead of I2C for communication between arduino.
2019-01-29 Init remote sub project
2019-02-12 Refactor bis
2019-02-12 refactor
2019-02-12 init radio
2019-02-13 modif 3d model
2019-02-20 Radio interrupt for pause
2019-02-27 interrupt & more communication
2019-03-03 More orders
2019-03-05 Memory optimisation & more orders.
2019-03-08 modif modéle
2019-03-22 Constants remote
2019-10-14 Update 3d model
2019-12-20 no message
2019-12-23 tests + doc
2019-12-25 Only 1 servo to open & close arms
2019-12-26 Support for lux sensor TSL2591 from adafruit
2019-12-26 check ceiling light state
2019-12-27 3D model changes
2020-01-14 debug mode on camera
2020-01-14 3d model update
2020-01-14 Init EasyEda electronic schematic
2020-01-14 review
2020-01-14 On avance
2020-01-15 open & close arm
2020-01-18 new paper box
2020-01-20 update & clean 3D model
2020-01-21 Init power & light section
2020-01-25 Update pcb schematic
2020-01-26 update pcb schematics
2020-02-02 update model & schematics
2020-02-02 advices from Gilou on PCB
2020-02-09 move to kicad
2020-02-09 clean
2020-02-10 kicad schematic & pcb v0.1
2020-02-12 correction schematic gilou
2020-02-13 remove unecessary easyeda schematics
2020-02-16 update, gilou dans la place
2020-02-16 update & refactor
2020-02-17 pcb finalized
2020-02-20 update after tests
2020-02-20 chemical recipes
2020-02-25 Update, code for the pcb version.
2020-03-30 update billboard
2020-04-20 Code for new pcb, new spider mechanism (3rd iteration), confinment day 36
2020-05-11 Update for new spider mechanism
2020-07-09 Update checmical recipes
2020-09-16 update camera V2
2020-09-23 update model for laser cut
2020-11-24 Nextion remote begin
2020-11-24 Files for lasercut parts
2021-01-10 Camera system V2
2021-03-14 I quit my job for this project \o/
2021-03-23 New paper feed.
2021-03-27 New try for cutting system
2021-04-13 new paper holder and cutter
